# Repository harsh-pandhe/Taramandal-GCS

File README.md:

# Taramandal

Taramandal is a drone light show platform: a choreography design studio and a
ground control station, built to scale from a handful of simulated drones up
to hundreds on a single machine.

Two products, one shared engine:

- **Studio** — design formations, sequence multi-formation shows, validate
  safety, export or transmit to a fleet.
- **GCS (Ground Control Station)** — connect to a fleet (real PX4/Gazebo or a
  vectorized simulator), launch/land/RTL, monitor live telemetry, and watch
  the show from three views: an operations dashboard, a georeferenced 3D
  globe, and a night-sky preview.

## Repo layout

```
packages/
  tara-core          shared safety limits, geometry, layout — Python
  tara-gcs           fleet manager: telemetry, safety monitors, playback — Python
  tara-sim           vectorized drone-fleet simulator (no PX4/Gazebo needed) — Python
  tara-studio        choreography engine: generators, validator, assignment — Python
  tara-web           GCS dashboard — React
  tara-studio-web    Studio design UI — React
apps/
  tara               the `tara` CLI orchestrator
sim/
  px4                PX4 + Gazebo SITL fleet launcher (real-flight-dynamics backend)
```

## Quickstart

```bash
python3 -m venv .venv && .venv/bin/pip install -r requirements.txt
(cd packages/tara-web && npm install)
(cd packages/tara-studio-web && npm install)

./tara doctor            # checks your environment first
./tara up --backend sim -n 20   # fleet + both APIs + both dashboards, one command
# Ctrl+C stops everything
```

`tara up --backend px4 -n 3` runs the same stack against real PX4 SITL +
Gazebo instead of the simulator (needs PX4-Autopilot built locally; see
[sim/px4/README.md](sim/px4/README.md) for the pinned version, a sudo-free
build recipe, and `tara doctor`'s coverage of this backend).

Once the GCS is up, the simulation itself can also be started and stopped from
the dashboard's Simulation Control Bar — pick a fleet size, hit **Launch Gazebo
SITL**, and watch the status pills — so running a show does not require a
terminal. `tara up` remains the developer path; the control bar is the operator
one. RViz can be launched the same way once a PX4 fleet is running.

### Signed show files

The GCS only accepts a trajectory upload that comes with an Ed25519 signature
from a key listed in `tara.toml`'s `[security].trusted_keys`; anything else is
refused with 403.

```bash
./tara keygen ~/.tara/studio.pem --signer "Your name"   # once; prints the tara.toml line to add
./tara sign show.json --key ~/.tara/studio.pem           # writes show.json.sig.json
```

In the dashboard, select `show.json` and `show.json.sig.json` together. To
accept unsigned legacy files, including Studio's **Send to GCS** until the
Studio signs its own exports, start the stack with `./tara up --allow-unsigned`.

Run the test suite:

```bash
pytest -m "not slow"     # full suite, ~20s
pytest                    # includes the 100-drone milestone test, ~90s
```

## Contributing

This repo is private and access is by invitation. If you've been added as a
collaborator, start with [CONTRIBUTING.md](CONTRIBUTING.md) — it covers scope,
branching, and how issues are assigned before you write any code.

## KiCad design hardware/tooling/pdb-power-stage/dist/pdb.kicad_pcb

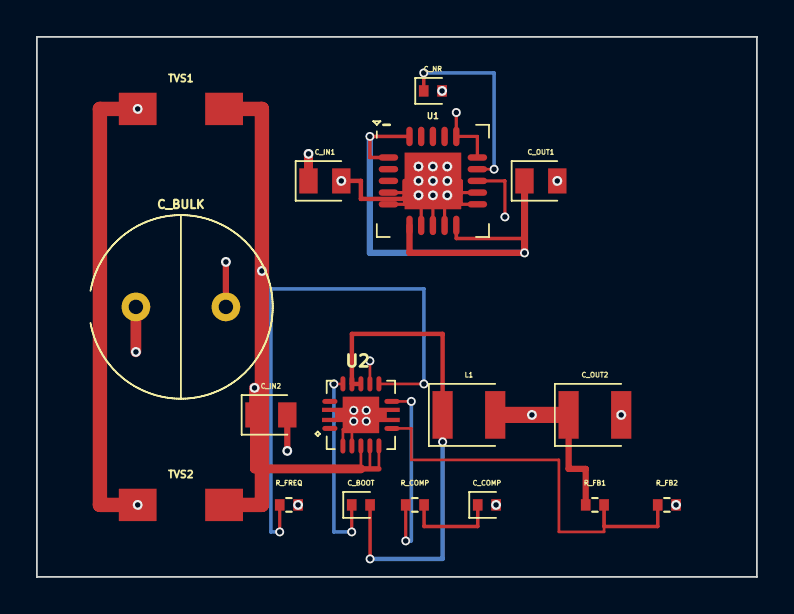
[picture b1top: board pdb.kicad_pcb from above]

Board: 4 copper layers, 40.0 x 30.0 mm, 17 parts (0 on the bottom side), 11 nets.

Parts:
C_BOOT: 100nF; capacitor_cap0402
C_BULK: 1000uF; capacitor_radial_10x20mm
C_COMP: 2.7nF; capacitor_cap0402
C_IN1, C_IN2: 10uF; capacitor_cap0805
C_NR: 10nF; capacitor_cap0402
C_OUT1: 10uF; capacitor_cap0805
C_OUT2: 47uF; capacitor_cap1210
L1: 2.2µH; inductor_1210
R_COMP: 12kΩ; resistor_res0402
R_FB1: 10.5kΩ; resistor_res0402
R_FB2: 2kΩ; resistor_res0402
R_FREQ: 100kΩ; resistor_res0402
TVS1, TVS2: SMAJ24A
U1: TPS7A4700RGWT
U2: TPS54620RGYR

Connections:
.L1 > .pin2 to .C_OUT2 > .pin1: C_OUT2.1, L1.2, R_FB1.1
.R_COMP > .pin2 to .C_COMP > .pin1: C_COMP.1, R_COMP.2
.R_FB1 > .pin2 to .R_FB2 > .pin1: R_FB1.2, R_FB2.1, U2.7
.TVS1 > .pin1 to .TVS2 > .pin1: C_BULK.2, C_COMP.2, C_IN1.2, C_IN2.2, C_NR.2, C_OUT1.2, C_OUT2.2, R_FB2.2, R_FREQ.2, TVS1.1, TVS2.1, U1.4, U1.5, U1.7, U1.8, U1.9, U1.11, U1.12, U1.21, U2.2, U2.3, U2.15
.TVS1 > .pin2 to .TVS2 > .pin2: C_BULK.1, C_IN1.1, C_IN2.1, TVS1.2, TVS2.2, U1.13, U1.15, U1.16, U2.4, U2.5, U2.6, U2.10
.U1 > .NR to .C_NR > .pin1: C_NR.1, U1.14
.U1 > .OUT1 to .U1 > .OUT2: C_OUT1.1, U1.1, U1.6, U1.10, U1.20
.U2 > .BOOT to .C_BOOT > .pin1: C_BOOT.1, U2.13
.U2 > .COMP to .R_COMP > .pin1: R_COMP.1, U2.8
.U2 > .PH1 to .U2 > .PH2: C_BOOT.2, L1.1, U2.11, U2.12
.U2 > .pin9 to .R_FREQ > .pin1: R_FREQ.1, U2.9

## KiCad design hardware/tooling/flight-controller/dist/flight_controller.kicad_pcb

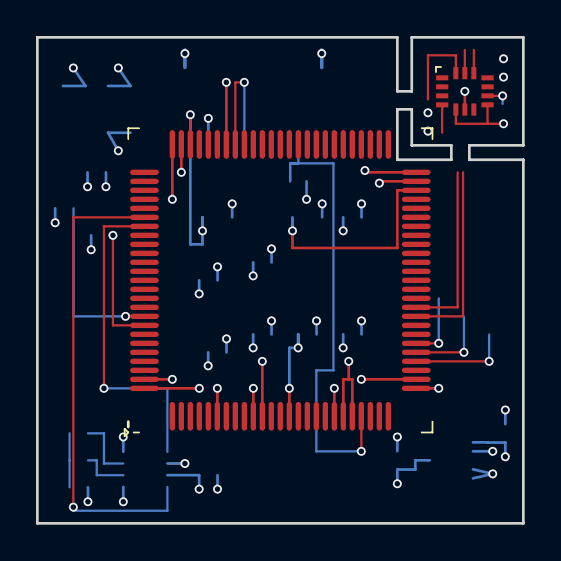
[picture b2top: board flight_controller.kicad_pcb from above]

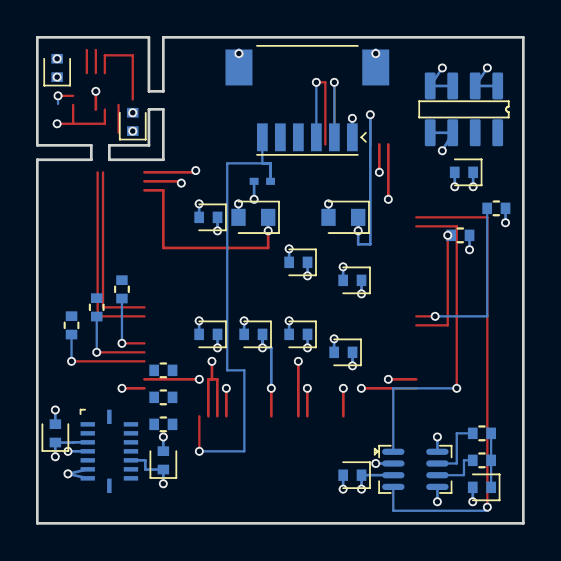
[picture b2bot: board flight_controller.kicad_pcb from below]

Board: 4 copper layers, 27.0 x 27.0 mm, 33 parts (31 on the bottom side), 31 nets.

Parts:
C_BARO_VDD: 100nF; capacitor_cap0402
C_CAN_SPLIT: 4.7nF; capacitor_cap0402
C_CAN_VCC: 100nF; capacitor_cap0402
C_IMU1_VDD, C_IMU1_VDDIO, C_IMU2_VDD, C_IMU2_VDDIO: 100nF; capacitor_cap0402
C_NRST: 100nF; capacitor_cap0402
C_VCAP1, C_VCAP2: 4.7uF; capacitor_cap0603
C_VDD1, C_VDD2, C_VDD3, C_VDD4, C_VDD5: 100nF; capacitor_cap0402
C_VDDA: 100nF; capacitor_cap0402
D_ESD_PPS: ESD9B5.0ST5G
J1: SM06B-SRSS-TB(LF)(SN)
R_CAN_SPLIT1, R_CAN_SPLIT2: 60.4Ω; resistor_res0402
R_I2C1_SCL, R_I2C1_SDA: 4.7kΩ; resistor_res0402
R_SPI1_MISO, R_SPI1_MOSI, R_SPI1_SCK, R_SPI2_MISO, R_SPI2_MOSI, R_SPI2_SCK: 22Ω; resistor_res0402
U1: STM32H743VIT6
U2: ICM-42688-P
U3: BMI088
U4: MS561101BA03-50
U5: TCAN334GDCNT

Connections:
.J1 > .pin2 to .U1 > .PA10: J1.2, U1.69
.J1 > .pin3 to .U1 > .PA9: J1.3, U1.68
.J1 > .pin4 to .U1 > .PB6: J1.4, R_I2C1_SCL.2, U1.92, U4.8
.J1 > .pin5 to .U1 > .PB7: J1.5, R_I2C1_SDA.2, U1.93, U4.7
.J1 > .pin6 to .D_ESD_PPS > .pin1: D_ESD_PPS.1, J1.6, U1.22
.R_CAN_SPLIT1 > .pin2 to .R_CAN_SPLIT2 > .pin2: C_CAN_SPLIT.1, R_CAN_SPLIT1.2, R_CAN_SPLIT2.2
.R_SPI1_MISO > .pin2 to .U2 > .pin9: R_SPI1_MISO.2, U2.9
.R_SPI1_MOSI > .pin2 to .U2 > .pin14: R_SPI1_MOSI.2, U2.14
.R_SPI1_SCK > .pin2 to .U2 > .pin13: R_SPI1_SCK.2, U2.13
.R_SPI2_MISO > .pin2 to .U3 > .SDO1: R_SPI2_MISO.2, U3.10, U3.15
.R_SPI2_MOSI > .pin2 to .U3 > .MOSI: R_SPI2_MOSI.2, U3.9
.R_SPI2_SCK > .pin2 to .U3 > .SCK: R_SPI2_SCK.2, U3.8
.U1 > .NRST to .C_NRST > .pin1: C_NRST.1, U1.14
.U1 > .PA5 to .R_SPI1_SCK > .pin1: R_SPI1_SCK.1, U1.29
.U1 > .PA6 to .R_SPI1_MISO > .pin1: R_SPI1_MISO.1, U1.30
.U1 > .PA7 to .R_SPI1_MOSI > .pin1: R_SPI1_MOSI.1, U1.31
.U1 > .PB0 to .U2 > .AP_CS: U1.34, U2.12
.U1 > .PB1 to .U2 > .pin4: U1.35, U2.4
.U1 > .PB11 to .U3 > .CSB2: U1.47, U3.5
.U1 > .PB12 to .U3 > .CSB1: U1.51, U3.14
.U1 > .PB13 to .R_SPI2_SCK > .pin1: R_SPI2_SCK.1, U1.52
.U1 > .PB14 to .R_SPI2_MISO > .pin1: R_SPI2_MISO.1, U1.53
.U1 > .PB15 to .R_SPI2_MOSI > .pin1: R_SPI2_MOSI.1, U1.54
.U1 > .PD0 to .U5 > .RXD: U1.81, U5.4
.U1 > .PD1 to .U5 > .TXD: U1.82, U5.1
.U1 > .VCAP1 to .C_VCAP1 > .pin1: C_VCAP1.1, U1.73
.U1 > .VCAP2 to .C_VCAP2 > .pin1: C_VCAP2.1, U1.48
.U1 > .VDD1 to .U1 > .VDD2: C_BARO_VDD.1, C_CAN_VCC.1, C_IMU1_VDD.1, C_IMU1_VDDIO.1, C_IMU2_VDD.1, C_IMU2_VDDIO.1, C_VDD1.1, C_VDD2.1, C_VDD3.1, C_VDD4.1, C_VDD5.1, C_VDDA.1, J1.1, R_I2C1_SCL.1, R_I2C1_SDA.1, U1.6, U1.11, U1.20, U1.21, U1.27, U1.50, U1.75, U1.100, U2.5, U2.8, U3.3, U3.11, U4.1, U4.2, U5.3
.U1 > .VSS1 to .U1 > .VSS2: C_BARO_VDD.2, C_CAN_SPLIT.2, C_CAN_VCC.2, C_IMU1_VDD.2, C_IMU1_VDDIO.2, C_IMU2_VDD.2, C_IMU2_VDDIO.2, C_NRST.2, C_VCAP1.2, C_VCAP2.2, C_VDD1.2, C_VDD2.2, C_VDD3.2, C_VDD4.2, C_VDD5.2, C_VDDA.2, D_ESD_PPS.2, J1.7, J1.8, U1.10, U1.19, U1.26, U1.49, U1.74, U1.99, U2.6, U3.4, U3.6, U3.7, U4.3, U4.4, U4.5, U4.6, U5.2, U5.5, U5.8
.U5 > .CANH to .R_CAN_SPLIT1 > .pin1: R_CAN_SPLIT1.1, U5.7
.U5 > .CANL to .R_CAN_SPLIT2 > .pin1: R_CAN_SPLIT2.1, U5.6

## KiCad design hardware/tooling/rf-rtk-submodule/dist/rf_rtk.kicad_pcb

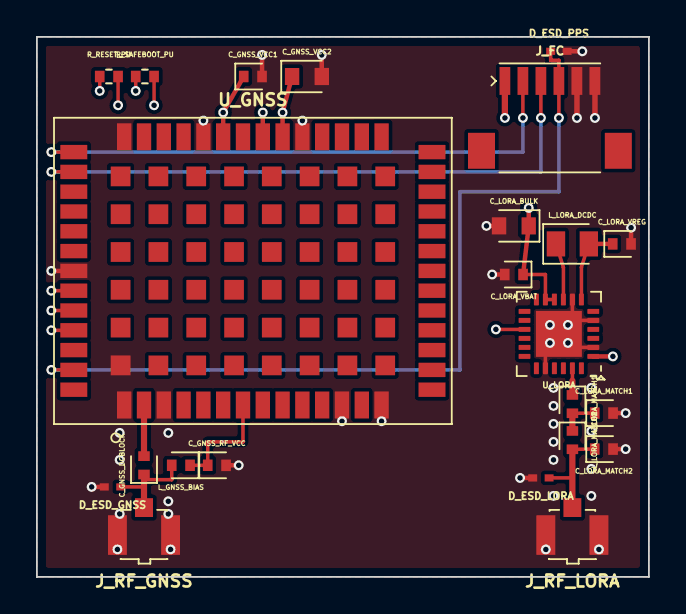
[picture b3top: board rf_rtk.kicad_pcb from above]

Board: 4 copper layers, 34.0 x 30.0 mm, 23 parts (0 on the bottom side), 16 nets.

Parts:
C_GNSS_DCBLOCK: 100nF; capacitor_cap0402
C_GNSS_RF_VCC: 100nF; capacitor_cap0402
C_GNSS_VCC1: 100nF; capacitor_cap0402
C_GNSS_VCC2: 10uF; capacitor_cap0603
C_LORA_BULK: 10uF; capacitor_cap0603
C_LORA_MATCH1: 2.7pF; capacitor_cap0402
C_LORA_MATCH2: 4.7pF; capacitor_cap0402
C_LORA_VBAT: 100nF; capacitor_cap0402
C_LORA_VREG: 470nF; capacitor_cap0402
D_ESD_GNSS: ESD9B5.0ST5G
D_ESD_LORA: ESD9B5.0ST5G
D_ESD_PPS: ESD9B5.0ST5G
J_FC: SM06B-SRSS-TB(LF)(SN)
J_RF_GNSS: U.FL-R-SMT-1(80)
J_RF_LORA: U.FL-R-SMT-1(80)
L_GNSS_BIAS: 47nH; inductor_0402
L_LORA_DCDC: 15µH; inductor_0805
L_LORA_MATCH1: 3.9nH; inductor_0402
L_LORA_MATCH2: 6.8nH; inductor_0402
R_RESET_PU: 10kΩ; resistor_res0402
R_SAFEBOOT_PU: 10kΩ; resistor_res0402
U_GNSS: ZED-F9P-04B
U_LORA: SX1262IMLTRT

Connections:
.C_GNSS_DCBLOCK > .pin2 to .U_GNSS > .pin2: C_GNSS_DCBLOCK.2, U_GNSS.2
.J_FC > .pin1 to .U_GNSS > .pin34: C_GNSS_VCC1.1, C_GNSS_VCC2.1, C_LORA_BULK.1, C_LORA_VBAT.1, J_FC.1, R_RESET_PU.1, R_SAFEBOOT_PU.1, U_GNSS.33, U_GNSS.34, U_GNSS.36, U_LORA.1, U_LORA.10, U_LORA.11
.J_FC > .pin2 to .U_GNSS > .pin42: J_FC.2, U_GNSS.42
.J_FC > .pin3 to .U_GNSS > .pin43: J_FC.3, U_GNSS.43
.J_FC > .pin5 to .J_FC > .pin6: C_GNSS_RF_VCC.2, C_GNSS_VCC1.2, C_GNSS_VCC2.2, C_LORA_BULK.2, C_LORA_MATCH1.2, C_LORA_MATCH2.2, C_LORA_VBAT.2, C_LORA_VREG.2, D_ESD_GNSS.2, D_ESD_LORA.2, D_ESD_PPS.2, J_FC.5, J_FC.6, J_RF_GNSS.2, J_RF_GNSS.3, J_RF_LORA.2, J_RF_LORA.3, U_GNSS.1, U_GNSS.3, U_GNSS.12, U_GNSS.14, U_GNSS.32, U_GNSS.37, U_GNSS.41, U_GNSS.48, U_GNSS.55, U_LORA.2, U_LORA.5, U_LORA.8, U_LORA.20, U_LORA.25
.J_RF_GNSS > .pin1 to .D_ESD_GNSS > .pin1: C_GNSS_DCBLOCK.1, D_ESD_GNSS.1, J_RF_GNSS.1, L_GNSS_BIAS.2
.L_LORA_DCDC > .pin2 to .U_LORA > .pin7: C_LORA_VREG.1, L_LORA_DCDC.2, U_LORA.7
.L_LORA_MATCH1 > .pin2 to .C_LORA_MATCH1 > .pin1: C_LORA_MATCH1.1, L_LORA_MATCH1.2, L_LORA_MATCH2.1
.L_LORA_MATCH2 > .pin2 to .C_LORA_MATCH2 > .pin1: C_LORA_MATCH2.1, D_ESD_LORA.1, J_RF_LORA.1, L_LORA_MATCH2.2
.R_RESET_PU > .pin2 to .U_GNSS > .pin49: R_RESET_PU.2, U_GNSS.49
.R_SAFEBOOT_PU > .pin2 to .U_GNSS > .pin50: R_SAFEBOOT_PU.2, U_GNSS.50
.U_GNSS > .pin7 to .L_GNSS_BIAS > .pin1: C_GNSS_RF_VCC.1, L_GNSS_BIAS.1, U_GNSS.7
.U_GNSS > .pin53 to .D_ESD_PPS > .pin1: D_ESD_PPS.1, J_FC.4, U_GNSS.53
.U_LORA > .pin9 to .L_LORA_DCDC > .pin1: L_LORA_DCDC.1, U_LORA.9
.U_LORA > .pin15 to .U_GNSS > .pin51: U_GNSS.51, U_LORA.15
.U_LORA > .pin23 to .L_LORA_MATCH1 > .pin1: L_LORA_MATCH1.1, U_LORA.23

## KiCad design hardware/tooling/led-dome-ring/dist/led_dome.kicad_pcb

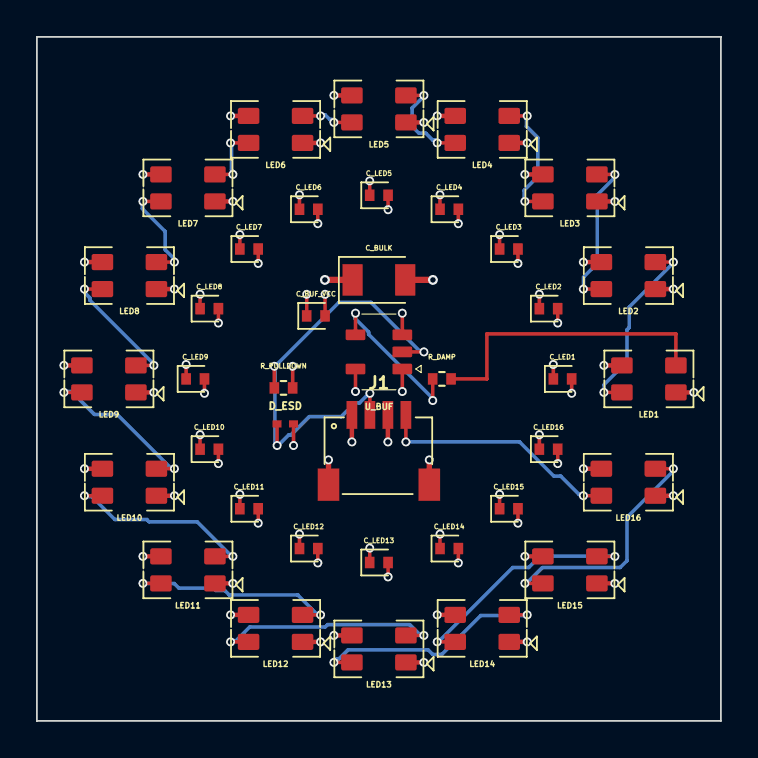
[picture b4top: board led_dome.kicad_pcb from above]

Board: 4 copper layers, 38.0 x 38.0 mm, 39 parts (0 on the bottom side), 21 nets.

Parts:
C_BUF_VCC: 100nF; capacitor_cap0402
C_BULK: 100uF; capacitor_cap1206
C_LED1, C_LED2, C_LED3, C_LED4, C_LED5, C_LED6, C_LED7, C_LED8, C_LED9, C_LED10, C_LED11, C_LED12, C_LED13, C_LED14, C_LED15, C_LED16: 100nF; capacitor_cap0402
D_ESD: ESD9B5.0ST5G
J1: SM04B-SRSS-TB(LF)(SN)
LED1, LED2, LED3, LED4, LED5, LED6, LED7, LED8, LED9, LED10, LED11, LED12, LED13, LED14, LED15, LED16: SK6812MINI-ER
R_DAMP: 47Ω; resistor_res0402
R_PULLDOWN: 10kΩ; resistor_res0402
U_BUF: SN74AHCT1G125DBVR

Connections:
.J1 > .pin1 to .C_BULK > .pin1: C_BUF_VCC.1, C_BULK.1, C_LED1.1, C_LED2.1, C_LED3.1, C_LED4.1, C_LED5.1, C_LED6.1, C_LED7.1, C_LED8.1, C_LED9.1, C_LED10.1, C_LED11.1, C_LED12.1, C_LED13.1, C_LED14.1, C_LED15.1, C_LED16.1, J1.1, LED1.3, LED2.3, LED3.3, LED4.3, LED5.3, LED6.3, LED7.3, LED8.3, LED9.3, LED10.3, LED11.3, LED12.3, LED13.3, LED14.3, LED15.3, LED16.3, U_BUF.5
.J1 > .pin2 to .D_ESD > .pin1: D_ESD.1, J1.2, R_PULLDOWN.1, U_BUF.2
.J1 > .pin3 to .J1 > .pin5: C_BUF_VCC.2, C_BULK.2, C_LED1.2, C_LED2.2, C_LED3.2, C_LED4.2, C_LED5.2, C_LED6.2, C_LED7.2, C_LED8.2, C_LED9.2, C_LED10.2, C_LED11.2, C_LED12.2, C_LED13.2, C_LED14.2, C_LED15.2, C_LED16.2, D_ESD.2, J1.3, J1.5, J1.6, LED1.1, LED2.1, LED3.1, LED4.1, LED5.1, LED6.1, LED7.1, LED8.1, LED9.1, LED10.1, LED11.1, LED12.1, LED13.1, LED14.1, LED15.1, LED16.1, R_PULLDOWN.2, U_BUF.1, U_BUF.3
.LED1 > .DOUT to .LED2 > .DIN: LED1.4, LED2.2
.LED2 > .DOUT to .LED3 > .DIN: LED2.4, LED3.2
.LED3 > .DOUT to .LED4 > .DIN: LED3.4, LED4.2
.LED4 > .DOUT to .LED5 > .DIN: LED4.4, LED5.2
.LED5 > .DOUT to .LED6 > .DIN: LED5.4, LED6.2
.LED6 > .DOUT to .LED7 > .DIN: LED6.4, LED7.2
.LED7 > .DOUT to .LED8 > .DIN: LED7.4, LED8.2
.LED8 > .DOUT to .LED9 > .DIN: LED8.4, LED9.2
.LED9 > .DOUT to .LED10 > .DIN: LED9.4, LED10.2
.LED10 > .DOUT to .LED11 > .DIN: LED10.4, LED11.2
.LED11 > .DOUT to .LED12 > .DIN: LED11.4, LED12.2
.LED12 > .DOUT to .LED13 > .DIN: LED12.4, LED13.2
.LED13 > .DOUT to .LED14 > .DIN: LED13.4, LED14.2
.LED14 > .DOUT to .LED15 > .DIN: LED14.4, LED15.2
.LED15 > .DOUT to .LED16 > .DIN: LED15.4, LED16.2
.LED16 > .DOUT to .J1 > .pin4: J1.4, LED16.4
.R_DAMP > .pin2 to .LED1 > .DIN: LED1.2, R_DAMP.2
.U_BUF > .Y to .R_DAMP > .pin1: R_DAMP.1, U_BUF.4

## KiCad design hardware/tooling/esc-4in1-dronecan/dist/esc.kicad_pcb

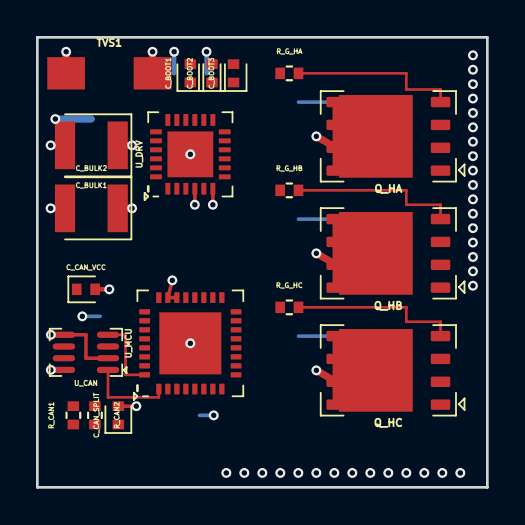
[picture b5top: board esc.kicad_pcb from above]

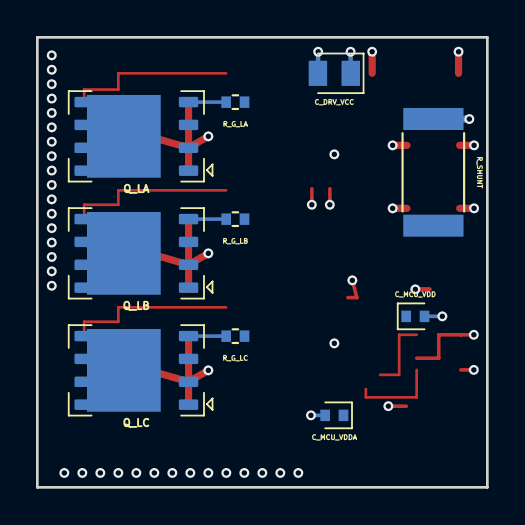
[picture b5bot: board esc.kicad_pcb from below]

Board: 4 copper layers, 25.0 x 25.0 mm, 29 parts (10 on the bottom side), 33 nets.

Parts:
C_BOOT1, C_BOOT2, C_BOOT3: 100nF; capacitor_cap0402
C_BULK1, C_BULK2: 22uF; capacitor_cap1210
C_CAN_SPLIT: 4.7nF; capacitor_cap0402
C_CAN_VCC: 100nF; capacitor_cap0402
C_DRV_VCC: 10uF; capacitor_cap0805
C_MCU_VDD: 100nF; capacitor_cap0402
C_MCU_VDDA: 100nF; capacitor_cap0402
Q_HA: AON6512
Q_HB: AON6512
Q_HC: AON6512
Q_LA: AON6512
Q_LB: AON6512
Q_LC: AON6512
R_CAN1, R_CAN2: 60.4Ω; resistor_res0402
R_G_HA: 4.7Ω; resistor_res0402
R_G_HB: 4.7Ω; resistor_res0402
R_G_HC: 4.7Ω; resistor_res0402
R_G_LA: 4.7Ω; resistor_res0402
R_G_LB: 4.7Ω; resistor_res0402
R_G_LC: 4.7Ω; resistor_res0402
R_SHUNT: 500µΩ; resistor_res2512
TVS1: SMAJ24A
U_CAN: TCAN334GDCNT
U_DRV: FD6288Q
U_MCU: STM32G071KBU6

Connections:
.R_CAN1 > .pin2 to .R_CAN2 > .pin2: C_CAN_SPLIT.1, R_CAN1.2, R_CAN2.2
.R_G_HA > .pin2 to .Q_HA > .pin4: Q_HA.4, R_G_HA.2
.R_G_HB > .pin2 to .Q_HB > .pin4: Q_HB.4, R_G_HB.2
.R_G_HC > .pin2 to .Q_HC > .pin4: Q_HC.4, R_G_HC.2
.R_G_LA > .pin2 to .Q_LA > .pin4: Q_LA.4, R_G_LA.2
.R_G_LB > .pin2 to .Q_LB > .pin4: Q_LB.4, R_G_LB.2
.R_G_LC > .pin2 to .Q_LC > .pin4: Q_LC.4, R_G_LC.2
.R_SHUNT > .pin1 to .Q_LA > .pin1: Q_LA.1, Q_LA.2, Q_LA.3, Q_LB.1, Q_LB.2, Q_LB.3, Q_LC.1, Q_LC.2, Q_LC.3, R_SHUNT.1, U_MCU.7
.TVS1 > .pin1 to .C_BULK1 > .pin2: C_BULK1.2, C_BULK2.2, C_CAN_SPLIT.2, C_CAN_VCC.2, C_DRV_VCC.2, C_MCU_VDD.2, C_MCU_VDDA.2, R_SHUNT.2, TVS1.1, U_CAN.2, U_CAN.5, U_CAN.8, U_DRV.6, U_DRV.25, U_MCU.22, U_MCU.23, U_MCU.33
.TVS1 > .pin2 to .C_BULK1 > .pin1: C_BULK1.1, C_BULK2.1, C_DRV_VCC.1, Q_HA.5, Q_HA.6, Q_HA.7, Q_HA.8, Q_HA.9, Q_HB.5, Q_HB.6, Q_HB.7, Q_HB.8, Q_HB.9, Q_HC.5, Q_HC.6, Q_HC.7, Q_HC.8, Q_HC.9, TVS1.2, U_DRV.4
.U_CAN > .CANH to .R_CAN1 > .pin1: R_CAN1.1, U_CAN.7
.U_CAN > .CANL to .R_CAN2 > .pin1: R_CAN2.1, U_CAN.6
.U_DRV > .HO1 to .R_G_HA > .pin1: R_G_HA.1, U_DRV.19
.U_DRV > .HO2 to .R_G_HB > .pin1: R_G_HB.1, U_DRV.16
.U_DRV > .HO3 to .R_G_HC > .pin1: R_G_HC.1, U_DRV.13
.U_DRV > .LO1 to .R_G_LA > .pin1: R_G_LA.1, U_DRV.11
.U_DRV > .LO2 to .R_G_LB > .pin1: R_G_LB.1, U_DRV.10
.U_DRV > .LO3 to .R_G_LC > .pin1: R_G_LC.1, U_DRV.9
.U_DRV > .VB1 to .C_BOOT1 > .pin1: C_BOOT1.1, U_DRV.20
.U_DRV > .VB2 to .C_BOOT2 > .pin1: C_BOOT2.1, U_DRV.17
.U_DRV > .VB3 to .C_BOOT3 > .pin1: C_BOOT3.1, U_DRV.14
.U_DRV > .VS1 to .Q_HA > .pin1: C_BOOT1.2, Q_HA.1, Q_HA.2, Q_HA.3, Q_LA.5, Q_LA.6, Q_LA.7, Q_LA.8, Q_LA.9, U_DRV.18
.U_DRV > .VS2 to .Q_HB > .pin1: C_BOOT2.2, Q_HB.1, Q_HB.2, Q_HB.3, Q_LB.5, Q_LB.6, Q_LB.7, Q_LB.8, Q_LB.9, U_DRV.15
.U_DRV > .VS3 to .Q_HC > .pin1: C_BOOT3.2, Q_HC.1, Q_HC.2, Q_HC.3, Q_LC.5, Q_LC.6, Q_LC.7, Q_LC.8, Q_LC.9, U_DRV.12
.U_MCU > .PA8 to .U_DRV > .HIN1: U_DRV.22, U_MCU.18
.U_MCU > .PA9 to .U_DRV > .HIN2: U_DRV.23, U_MCU.19
.U_MCU > .PA10 to .U_DRV > .HIN3: U_DRV.24, U_MCU.21
.U_MCU > .PB0 to .U_DRV > .LIN1: U_DRV.1, U_MCU.15
.U_MCU > .PB1 to .U_DRV > .LIN2: U_DRV.2, U_MCU.16
.U_MCU > .PB2 to .U_DRV > .LIN3: U_DRV.3, U_MCU.17
.U_MCU > .PB8 to .U_CAN > .RXD: U_CAN.4, U_MCU.32
.U_MCU > .PB9 to .U_CAN > .TXD: U_CAN.1, U_MCU.1
.U_MCU > .pin4 to .U_MCU > .pin5: C_CAN_VCC.1, C_MCU_VDD.1, C_MCU_VDDA.1, U_CAN.3, U_MCU.4, U_MCU.5
